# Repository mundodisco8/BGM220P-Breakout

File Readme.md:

View this project on [CADLAB.io](https://cadlab.io/project/26395). 

# BGMP220P Breakout Board

## What's this?

A breakout board for Silicon Labs BGM220P bluetooth modules.

It's made with both WGA and HNA variants (352KB and 512KB flash sizes) in mind.

## How to use it?

### Making some

Gerbers should be available in the Releases section. Just grab them and print them. Keep in mind that it's a four layer board, and not all the cheap PCB manufacturers offer stupidly cheap 4 layer PCBs (although some do, and those who don't offer relatively cheap 4 layer boards).

Soldering is straightforward as pads have been extended for easier hand-soldering. A stencil made from these gerbers should only leave paste in part of the pads (by design). While I haven't tested it, it should be enough for hot air reflow or hotplate soldering.

### Add the target /  receptacle to you project, so you can add the module to your project.

The project includes a library with the "receptacle", two 1x16 headers spaced the required amount of distance. Place that in your board and plug your breakout. Alternatively, don't place headers, align hole to hole and apply solder.

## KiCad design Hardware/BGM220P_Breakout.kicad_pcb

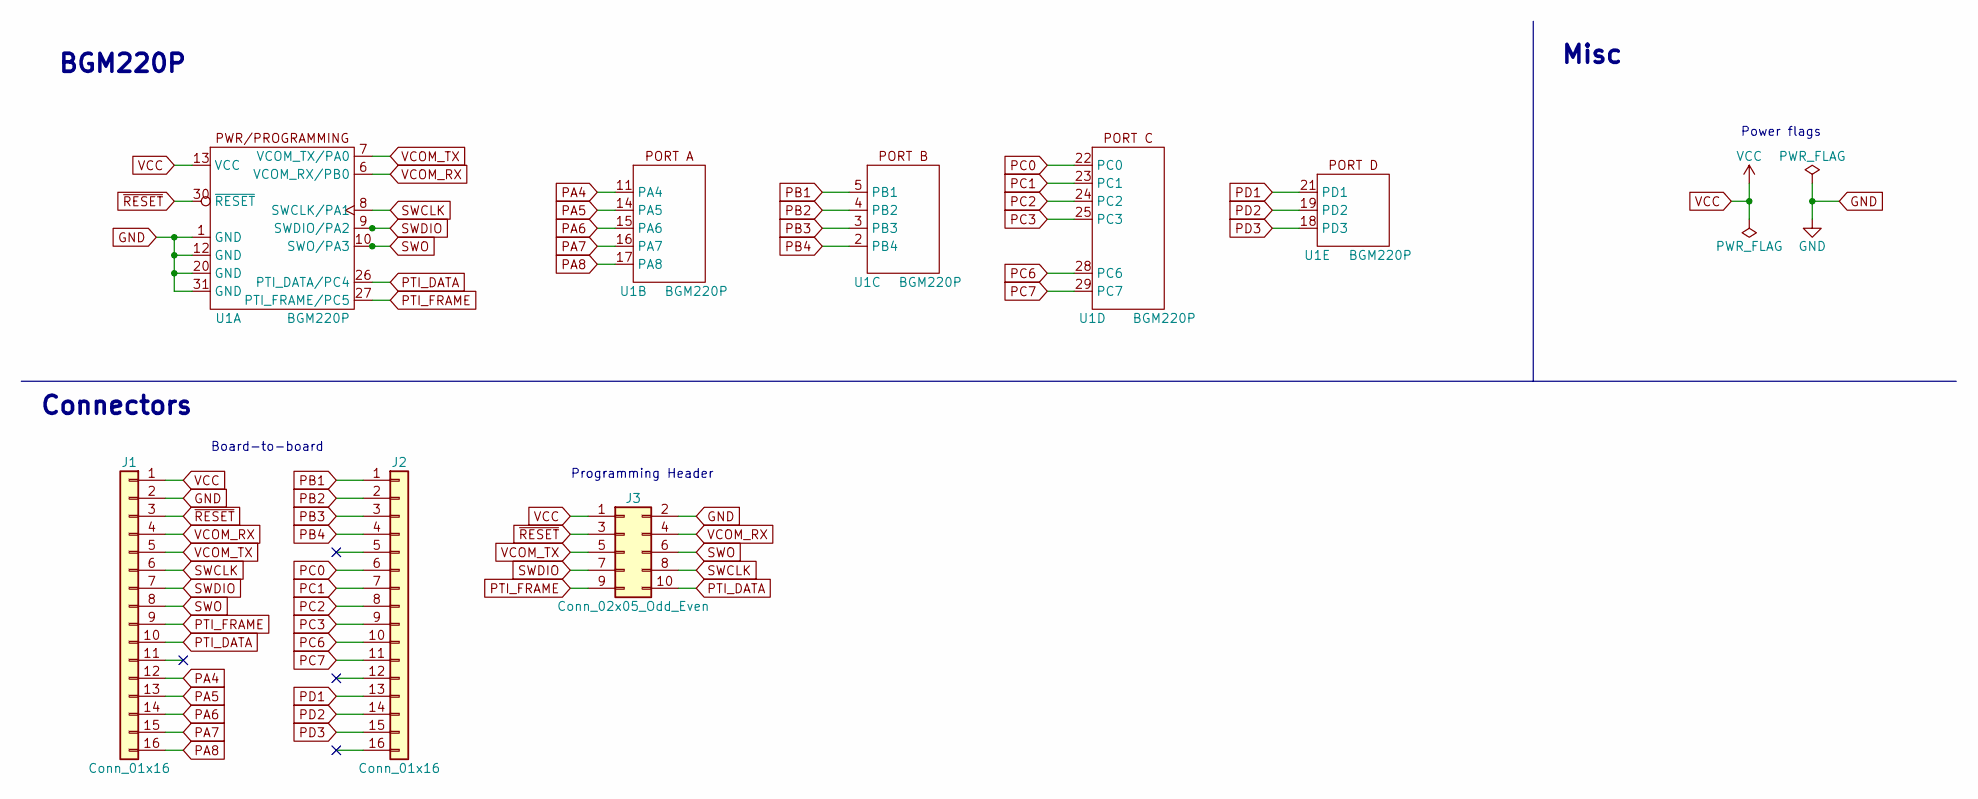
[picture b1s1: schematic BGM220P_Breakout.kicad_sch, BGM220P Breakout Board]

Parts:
J1, J2: Conn_01x16; PinHeader_1x16_P1.27mm_Vertical_Offset
J3: Conn_02x05_Odd_Even; PinHeader_2x05_P1.27mm_Vertical_SMD
U1: BGM220P

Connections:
GND: J1.2, J3.2, U1.1 (GND), U1.12 (GND), U1.20 (GND), U1.31 (GND)
PA4: J1.12, U1.11 (PA4)
PA5: J1.13, U1.14 (PA5)
PA6: J1.14, U1.15 (PA6)
PA7: J1.15, U1.16 (PA7)
PA8: J1.16, U1.17 (PA8)
PB1: J2.1, U1.5 (PB1)
PB2: J2.2, U1.4 (PB2)
PB3: J2.3, U1.3 (PB3)
PB4: J2.4, U1.2 (PB4)
PC0: J2.6, U1.22 (PC0)
PC1: J2.7, U1.23 (PC1)
PC2: J2.8, U1.24 (PC2)
PC3: J2.9, U1.25 (PC3)
PC6: J2.10, U1.28 (PC6)
PC7: J2.11, U1.29 (PC7)
PD1: J2.13, U1.21 (PD1)
PD2: J2.14, U1.19 (PD2)
PD3: J2.15, U1.18 (PD3)
PTI_DATA: J1.10, J3.10, U1.26 (PTI_DATA/PC4)
PTI_FRAME: J1.9, J3.9, U1.27 (PTI_FRAME/PC5)
SWCLK: J1.6, J3.8, U1.8 (SWCLK/PA1)
SWDIO: J1.7, J3.7, U1.9 (SWDIO/PA2)
SWO: J1.8, J3.6, U1.10 (SWO/PA3)
VCC: J1.1, J3.1, U1.13 (VCC)
VCOM_RX: J1.4, J3.4, U1.6 (VCOM_RX/PB0)
VCOM_TX: J1.5, J3.5, U1.7 (VCOM_TX/PA0)
~RESET: J1.3, J3.3, U1.30 (~RESET)

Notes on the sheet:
Connectors
Programming Header
Power flags
Misc
Board-to-board
BGM220P

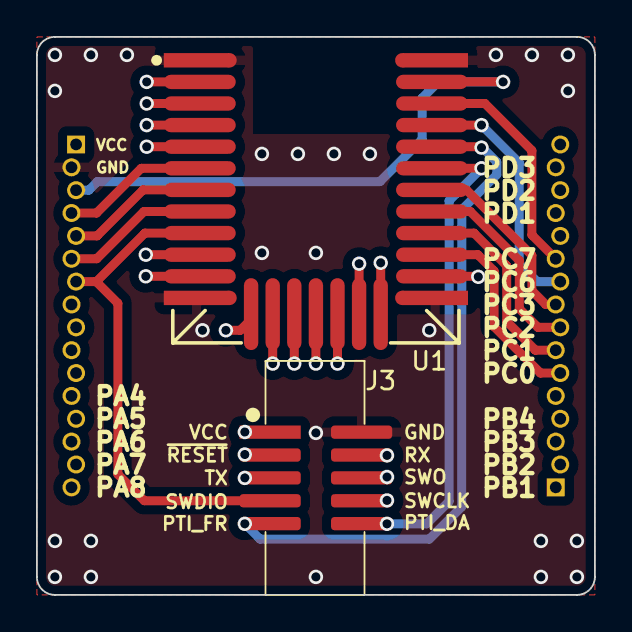
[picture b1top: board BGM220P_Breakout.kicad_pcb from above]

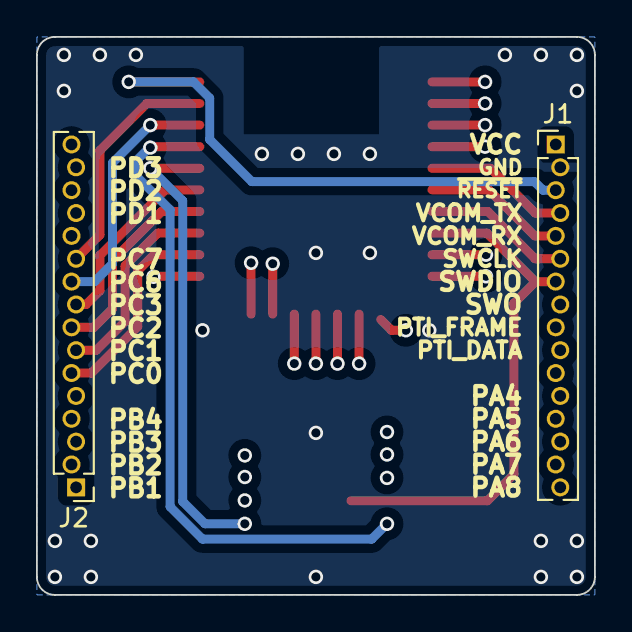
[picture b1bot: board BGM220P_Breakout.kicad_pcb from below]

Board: 4 copper layers, 31.0 x 31.0 mm, 4 parts (2 on the bottom side), 28 nets.

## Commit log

2023-01-12 Added environmental vars to get hash and date on prints
2023-01-12 Adding ACKs for warnings on the CICD
2023-01-12 Adding ACKs for warnings on the CICD, pt2
2023-01-12 Adding ACKs for warnings on the CICD, pt3
2023-01-13 Fixing CICD
2023-01-13 Increasing via diameter to 0.5mm
2023-01-13 Increasing via diameter to 0.5mm (again)
2023-01-16 Backlink to CADLAB.io has been added.
2023-01-17 Update Readme.md
    Updated Readme, images had broken links
2023-01-29 Updated receptacle footprint as pin numbering was wrong
2023-02-02 Changed the header footprint and added a 3D model
2023-02-10 Fixed header footprint with wrong pins, added SMD header, and library tidy up
2023-02-10 Trigger Github Actions on library file modification too!
